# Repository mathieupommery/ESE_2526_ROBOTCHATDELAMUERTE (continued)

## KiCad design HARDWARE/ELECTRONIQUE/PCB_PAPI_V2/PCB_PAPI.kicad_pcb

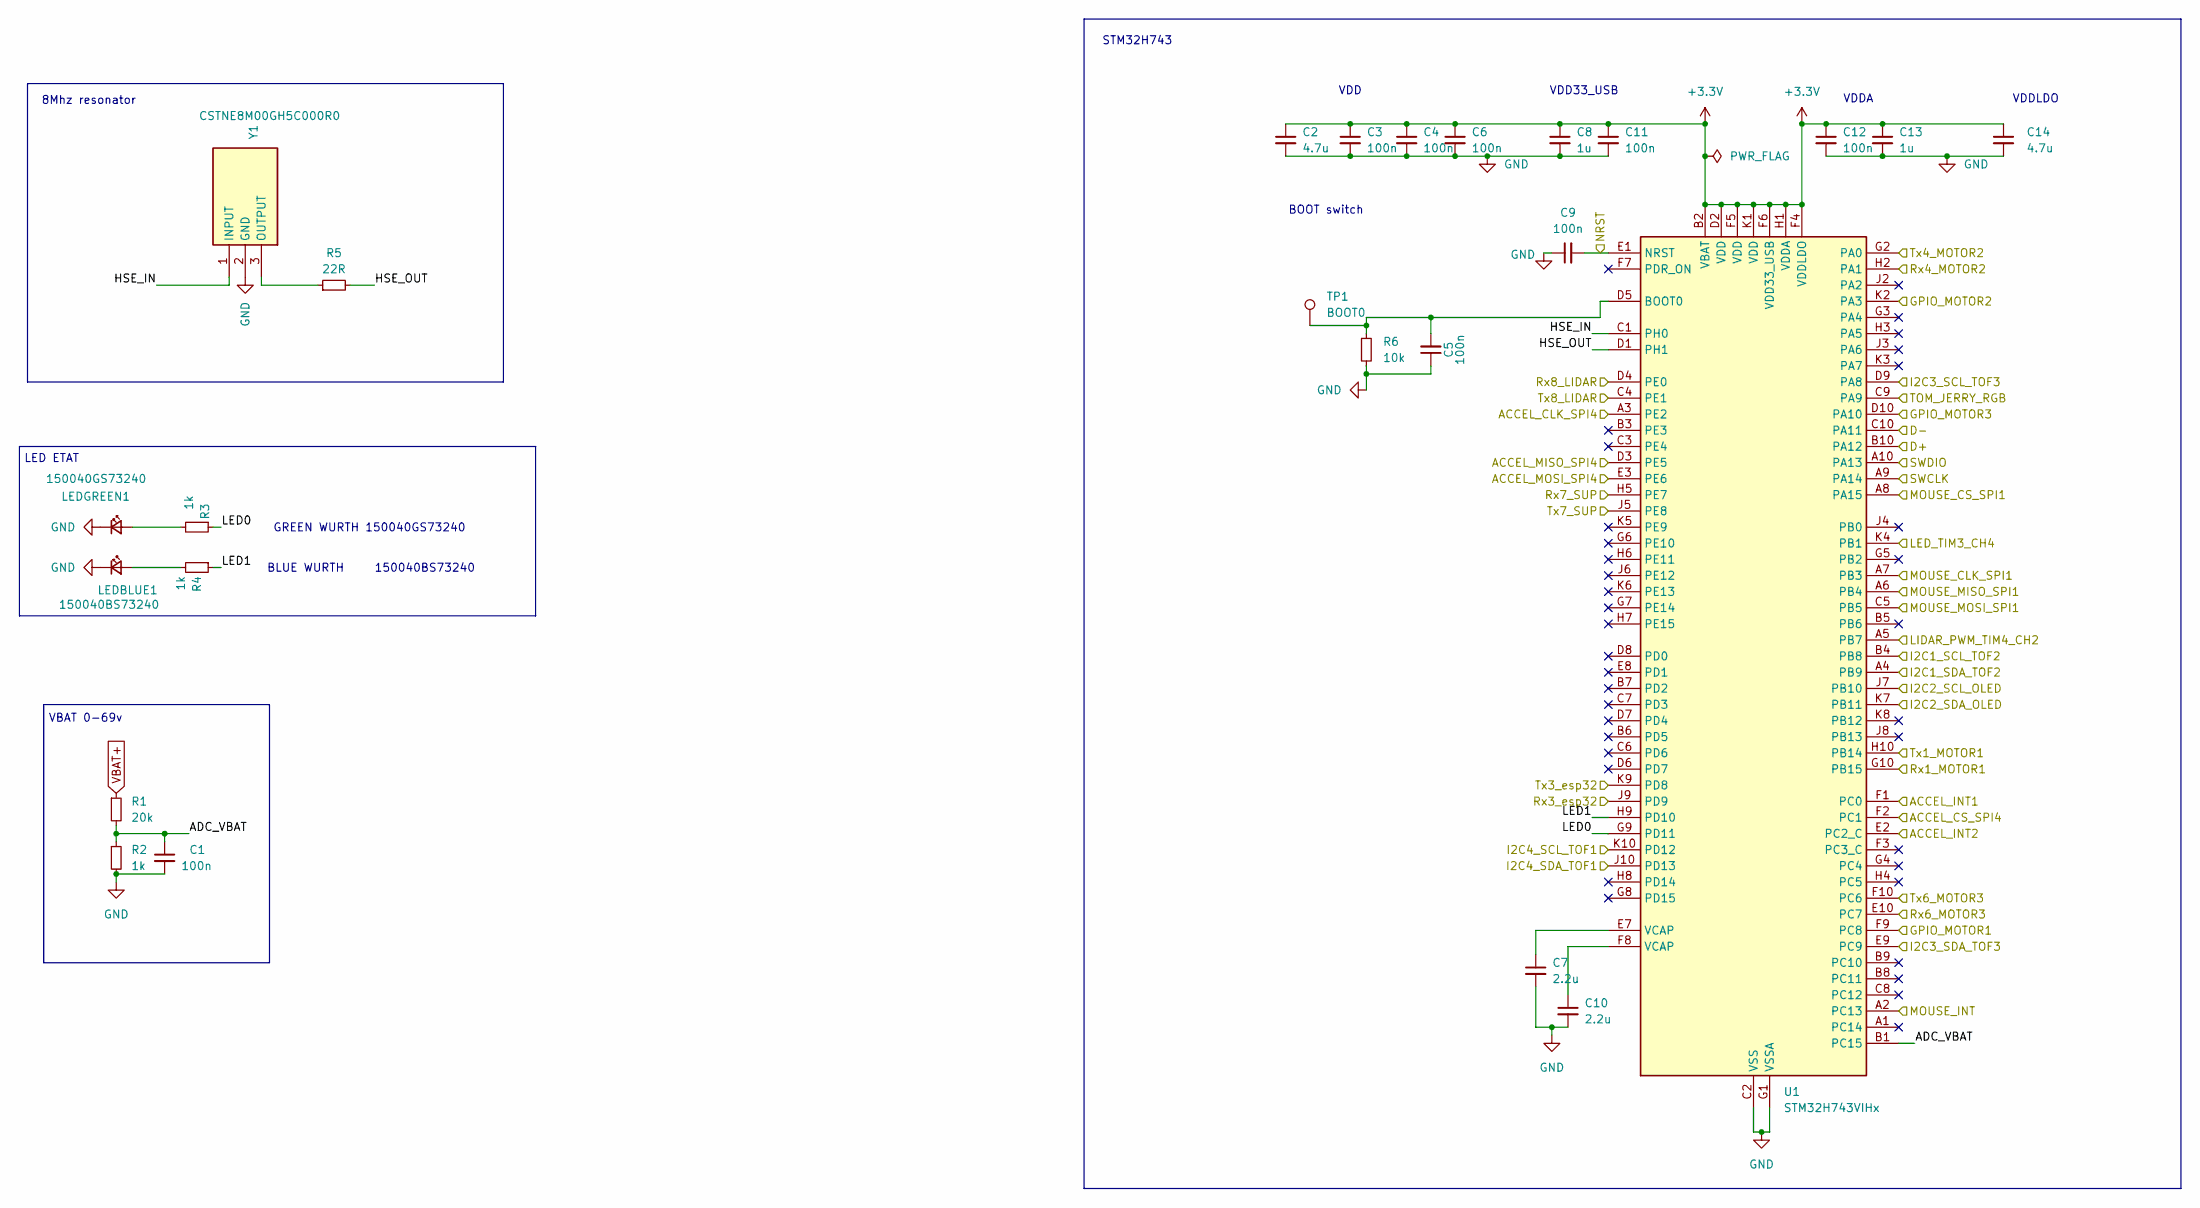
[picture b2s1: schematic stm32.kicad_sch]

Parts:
C1, C3, C5, C9: 100n; C_0201_custom; Manufacturer_Part_Number 885012104005; Mouser Part Number 710-885012104005
C2, C14: 4.7u; C_0402_1005Metric; Manufacturer_Part_Number 885012105008; Mouser Part Number 710-885012105008
C4, C6, C11, C12: 100n; C_0201_0603Metric; Manufacturer_Part_Number 885012104005; Mouser Part Number 710-885012104005
C7, C10: 2.2u; C_0402_1005Metric; Manufacturer_Part_Number 885012105007; Mouser Part Number 710-885012105007
C8, C13: 1u; C_0402_1005Metric; Manufacturer_Part_Number 885012105012; Mouser Part Number 710-885012105012
LEDBLUE1: 150040BS73240; LED_0402_1005Metric; Manufacturer_Part_Number 150040BS73240; Mouser Part Number 710-150040BS73240
LEDGREEN1: 150040GS73240; LED_0402_1005Metric; Manufacturer_Part_Number 150040GS73240; Mouser Part Number 710-150040GS73240
R1: 20k; R_0201_0603Metric; Manufacturer_Part_Number ERJ-1GNF2002C; Mouser Part Number 667-ERJ-1GNF2002C
R2: 1k; R_0201_custom; Manufacturer_Part_Number ERJ-1GNF1001C; Mouser Part Number 667-ERJ-1GNF1001C
R3, R4: 1k; R_0201_0603Metric; Manufacturer_Part_Number ERJ-1GNF1001C; Mouser Part Number 667-ERJ-1GNF1001C
R5: 22R; R_0201_0603Metric; Manufacturer_Part_Number ERJ-1GNF22R0C; Mouser Part Number 667-ERJ-1GNF22R0C
R6: 10k; R_0201_custom; Manufacturer_Part_Number ERJ-1GNF1002C; Mouser Part Number 667-ERJ-1GNF1002C
TP1: BOOT0; pad_0.7mm
U1: STM32H743VIHx; TFBGA-100_8x8mm_Layout10x10_P0.8mm; Manufacturer_Part_Number STM32H743VIH6; Mouser Part Number 511-STM32H743VIH6
Y1: CSTNE8M00GH5C000R0; CSTNE12M0GH5L000R0; Mouser Part Number 81-CSTNE8M00GH5C000R

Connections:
+3.3V: C2.1, C3.1, C4.1, C6.1, C8.1, C11.1, C12.1, C13.1, C14.1, U1.B2 (VBAT), U1.D2 (VDD), U1.F4 (VDDLDO), U1.F5 (VDD), U1.F6 (VDD33_USB), U1.H1 (VDDA), U1.K1 (VDD); also elsewhere on the board
/ACCEL_CLK: U1.A3 (PE2); also elsewhere on the board
/ACCEL_CS: U1.F2 (PC1); also elsewhere on the board
/ACCEL_INT1: U1.F1 (PC0); also elsewhere on the board
/ACCEL_INT2: U1.E2 (PC2_C); also elsewhere on the board
/ACCEL_MISO: U1.D3 (PE5); also elsewhere on the board
/ACCEL_MOSI: U1.E3 (PE6); also elsewhere on the board
/D+STM32: U1.B10 (PA12); also elsewhere on the board
/D-STM32: U1.C10 (PA11); also elsewhere on the board
/ESP32_RX: U1.K9 (PD8); also elsewhere on the board
/ESP32_TX: U1.J9 (PD9); also elsewhere on the board
/GPIO_MOT1: U1.F9 (PC8); also elsewhere on the board
/GPIO_MOT2: U1.K2 (PA3); also elsewhere on the board
/GPIO_MOT3: U1.D10 (PA10); also elsewhere on the board
/LED_TIM: U1.K4 (PB1); also elsewhere on the board
/LIDAR_PWM: U1.A5 (PB7); also elsewhere on the board
/MOUSE_CLK: U1.A7 (PB3); also elsewhere on the board
/MOUSE_CS: U1.A8 (PA15); also elsewhere on the board
/MOUSE_INT: U1.A2 (PC13); also elsewhere on the board
/MOUSE_MISO: U1.A6 (PB4); also elsewhere on the board
/MOUSE_MOSI: U1.C5 (PB5); also elsewhere on the board
/NRST: C9.2, U1.E1 (NRST); also elsewhere on the board
/RGB_TOM_JERRY: U1.C9 (PA9); also elsewhere on the board
/RX_LIDAR: U1.D4 (PE0); also elsewhere on the board
/RX_MOT1: U1.G10 (PB15); also elsewhere on the board
/RX_MOT2: U1.H2 (PA1); also elsewhere on the board
/RX_MOT3: U1.E10 (PC7); also elsewhere on the board
/RX_SUP: U1.H5 (PE7); also elsewhere on the board
/SCL_OLED: U1.J7 (PB10); also elsewhere on the board
/SCL_TOF1: U1.K10 (PD12); also elsewhere on the board
/SCL_TOF2: U1.B4 (PB8); also elsewhere on the board
/SCL_TOF3: U1.D9 (PA8); also elsewhere on the board
/SDA_OLED: U1.K7 (PB11); also elsewhere on the board
/SDA_TOF1: U1.J10 (PD13); also elsewhere on the board
/SDA_TOF2: U1.A4 (PB9); also elsewhere on the board
/SDA_TOF3: U1.E9 (PC9); also elsewhere on the board
/STM32/ADC_VBAT: C1.1, R1.2, R2.1, U1.B1 (PC15)
/STM32/HSE_IN: U1.C1 (PH0), Y1.1 (INPUT)
/STM32/HSE_OUT: R5.2, U1.D1 (PH1)
/STM32/LED0: R3.1, U1.G9 (PD11)
/STM32/LED1: R4.1, U1.H9 (PD10)
/STM32/Tx8_LIDAR: U1.C4 (PE1)
/SWCLK: U1.A9 (PA14); also elsewhere on the board
/SWDIO: U1.A10 (PA13); also elsewhere on the board
/TX_MOT1: U1.H10 (PB14); also elsewhere on the board
/TX_MOT2: U1.G2 (PA0); also elsewhere on the board
/TX_MOT3: U1.F10 (PC6); also elsewhere on the board
/TX_SUP: U1.J5 (PE8); also elsewhere on the board
GND: C1.2, C2.2, C3.2, C4.2, C5.1, C6.2, C7.2, C8.2, C9.1, C10.2, C11.2, C12.2, C13.2, C14.2, LEDBLUE1.1 (K), LEDGREEN1.1 (K), R2.2, R6.2, U1.C2 (VSS), U1.E4 (VSS), U1.E5 (VSS), U1.E6 (VSS), U1.G1 (VSSA), U1.J1 (VSS), Y1.2 (GND); also elsewhere on the board
unnamed: C7.1, U1.E7 (VCAP)
unnamed: C10.1, U1.F8 (VCAP)
unnamed: LEDBLUE1.2 (A), R4.2
unnamed: LEDGREEN1.2 (A), R3.2
unnamed: C5.2, R6.1, TP1.1, U1.D5 (BOOT0)
unnamed: R5.1, Y1.3 (OUTPUT)
VBAT+: R1.1; also elsewhere on the board

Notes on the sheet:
8Mhz resonator
STM32H743
VDD
GREEN WURTH 150040GS73240
VDDA
BOOT switch
LED ETAT
VDD33_USB
VBAT 0-69v
BLUE WURTH 150040BS73240
VDDLDO

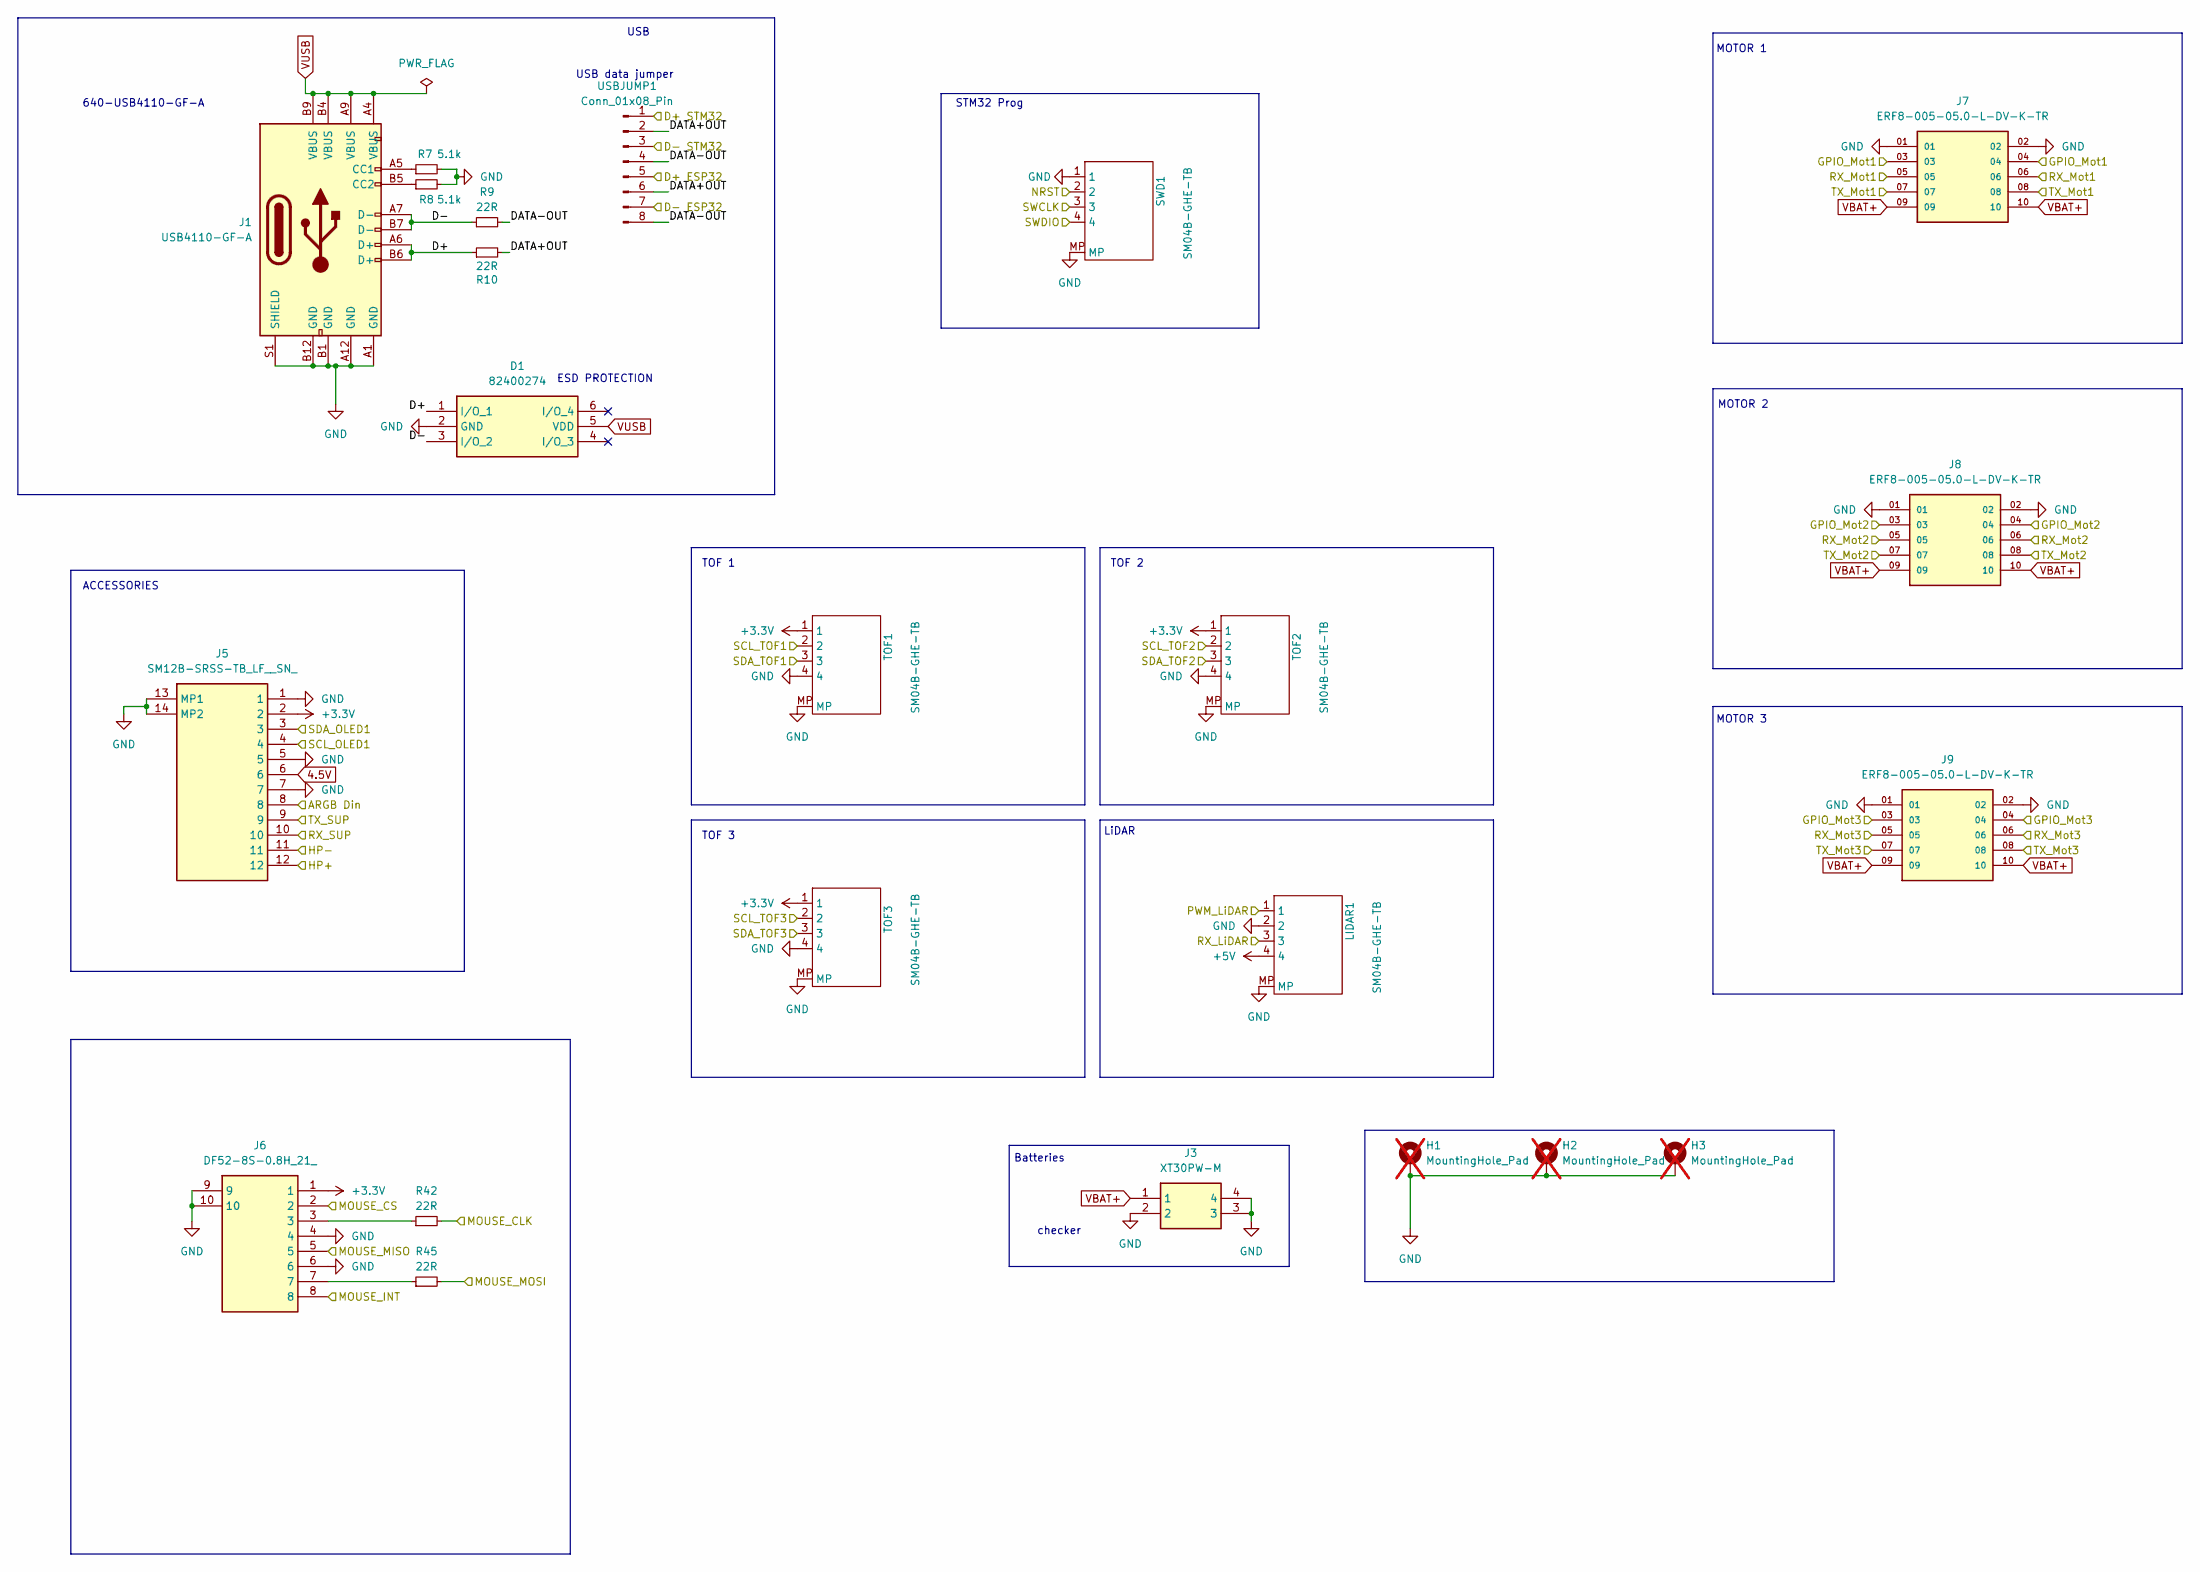
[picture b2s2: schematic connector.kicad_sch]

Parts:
D1: 82400274; SOT65P210X110-6N; Mouser Part Number 710-82400274
H1, H2, H3: MountingHole_Pad; MountingHole_2.5mm_Pad_Via; not fitted
J1: USB4110-GF-A; USB_C_Receptacle_GCT_USB4110; Manufacturer_Part_Number USB4110-GF-A; Mouser Part Number 640-USB4110-GF-A
J3: XT30PW-M; XT30PWM; Manufacturer_Part_Number XT30PW-M
J5: SM12B-SRSS-TB_LF__SN_; SM12BSRSSTBLFSN; Manufacturer_Part_Number SM12B-SRSS-TB(LF)(SN); Mouser Part Number N/A
J6: DF52-8S-0.8H_21_; DF528S08H21; Manufacturer_Part_Number DF52-8S-0.8H(21); Mouser Part Number 798-DF52-8S-0.8H21
J7, J8, J9: ERF8-005-05.0-L-DV-K-TR; SAMTEC_ERF8-005-05.0-L-DV-K-TR
LIDAR1: SM04B-GHE-TB; JST_GH_BM04B-GHS-TBT_1x04-1MP_P1.25mm_Vertical; Manufacturer_Part_Number SM04B-GHE-TB; Mouser Part Number 306-SM04BGHETBLFSN
R7, R8: 5.1k; R_0201_custom; Manufacturer_Part_Number ERJ-1GNF5101C; Mouser Part Number 667-ERJ-1GNF5101C
R9, R10, R42, R45: 22R; R_0201_0603Metric; Manufacturer_Part_Number ERJ-1GNF22R0C; Mouser Part Number 667-ERJ-1GNF22R0C
SWD1: SM04B-GHE-TB; JST_GH_BM04B; Manufacturer_Part_Number SM04B-GHE-TB; Mouser Part Number 306-SM04BGHETBLFSN
TOF1, TOF2, TOF3: SM04B-GHE-TB; JST_GH_BM04B; Manufacturer_Part_Number SM04B-GHE-TB; Mouser Part Number 306-SM04BGHETBLFSN
USBJUMP1: Conn_01x08_Pin; PinHeader_2x04_P1.27mm_Vertical_SMD

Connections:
4.5V: J5.6; also elsewhere on the board
+3.3V: J5.2, J6.1, TOF1.1, TOF2.1, TOF3.1; also elsewhere on the board
+5V: LIDAR1.4; also elsewhere on the board
/CONNECTOR/D+: D1.1 (I/O_1), J1.A6 (D+), J1.B6 (D+), R10.1
/CONNECTOR/D-: D1.3 (I/O_2), J1.A7 (D-), J1.B7 (D-), R9.1
/CONNECTOR/DATA+OUT: R10.2, USBJUMP1.2, USBJUMP1.6
/CONNECTOR/DATA-OUT: R9.2, USBJUMP1.4, USBJUMP1.8
/D+ESP32: USBJUMP1.5; also elsewhere on the board
/D+STM32: USBJUMP1.1; also elsewhere on the board
/D-ESP32: USBJUMP1.7; also elsewhere on the board
/D-STM32: USBJUMP1.3; also elsewhere on the board
/GPIO_MOT1: J7.03, J7.04; also elsewhere on the board
/GPIO_MOT2: J8.03, J8.04; also elsewhere on the board
/GPIO_MOT3: J9.03, J9.04; also elsewhere on the board
/HP+: J5.12; also elsewhere on the board
/HP-: J5.11; also elsewhere on the board
/LED_TIM: J5.8; also elsewhere on the board
/LIDAR_PWM: LIDAR1.1; also elsewhere on the board
/MOUSE_CLK: R42.2; also elsewhere on the board
/MOUSE_CS: J6.2; also elsewhere on the board
/MOUSE_INT: J6.8; also elsewhere on the board
/MOUSE_MISO: J6.5; also elsewhere on the board
/MOUSE_MOSI: R45.2; also elsewhere on the board
/NRST: SWD1.2; also elsewhere on the board
/RX_LIDAR: LIDAR1.3; also elsewhere on the board
/RX_MOT1: J7.05, J7.06; also elsewhere on the board
/RX_MOT2: J8.05, J8.06; also elsewhere on the board
/RX_MOT3: J9.05, J9.06; also elsewhere on the board
/RX_SUP: J5.10; also elsewhere on the board
/SCL_OLED: J5.4; also elsewhere on the board
/SCL_TOF1: TOF1.2; also elsewhere on the board
/SCL_TOF2: TOF2.2; also elsewhere on the board
/SCL_TOF3: TOF3.2; also elsewhere on the board
/SDA_OLED: J5.3; also elsewhere on the board
/SDA_TOF1: TOF1.3; also elsewhere on the board
/SDA_TOF2: TOF2.3; also elsewhere on the board
/SDA_TOF3: TOF3.3; also elsewhere on the board
/SWCLK: SWD1.3; also elsewhere on the board
/SWDIO: SWD1.4; also elsewhere on the board
/TX_MOT1: J7.07, J7.08; also elsewhere on the board
/TX_MOT2: J8.07, J8.08; also elsewhere on the board
/TX_MOT3: J9.07, J9.08; also elsewhere on the board
/TX_SUP: J5.9; also elsewhere on the board
GND: D1.2 (GND), H1.1, H2.1, H3.1, J1.A1 (GND), J1.A12 (GND), J1.B1 (GND), J1.B12 (GND), J1.S1 (SHIELD), J3.2, J3.3, J3.4, J5.1, J5.5, J5.7, J5.13 (MP1), J5.14 (MP2), J6.4, J6.6, J6.9, J6.10, J7.01, J7.02, J8.01, J8.02, J9.01, J9.02, LIDAR1.2, LIDAR1.MP, R7.2, R8.2, SWD1.1, SWD1.MP, TOF1.4, TOF1.MP, TOF2.4, TOF2.MP, TOF3.4, TOF3.MP; also elsewhere on the board
unnamed: J1.A5 (CC1), R7.1
unnamed: J1.B5 (CC2), R8.1
unnamed: J6.3, R42.1
unnamed: J6.7, R45.1
VBAT+: J3.1, J7.09, J7.10, J8.09, J8.10, J9.09, J9.10; also elsewhere on the board
VUSB: D1.5 (VDD), J1.A4 (VBUS), J1.A9 (VBUS), J1.B4 (VBUS), J1.B9 (VBUS); also elsewhere on the board

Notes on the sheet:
Batteries
TOF 2
LiDAR
ACCESSORIES
checker
USB data jumper
MOTOR 2
MOTOR 3
TOF 1
640-USB4110-GF-A
TOF 3
STM32 Prog
USB
MOTOR 1
ESD PROTECTION

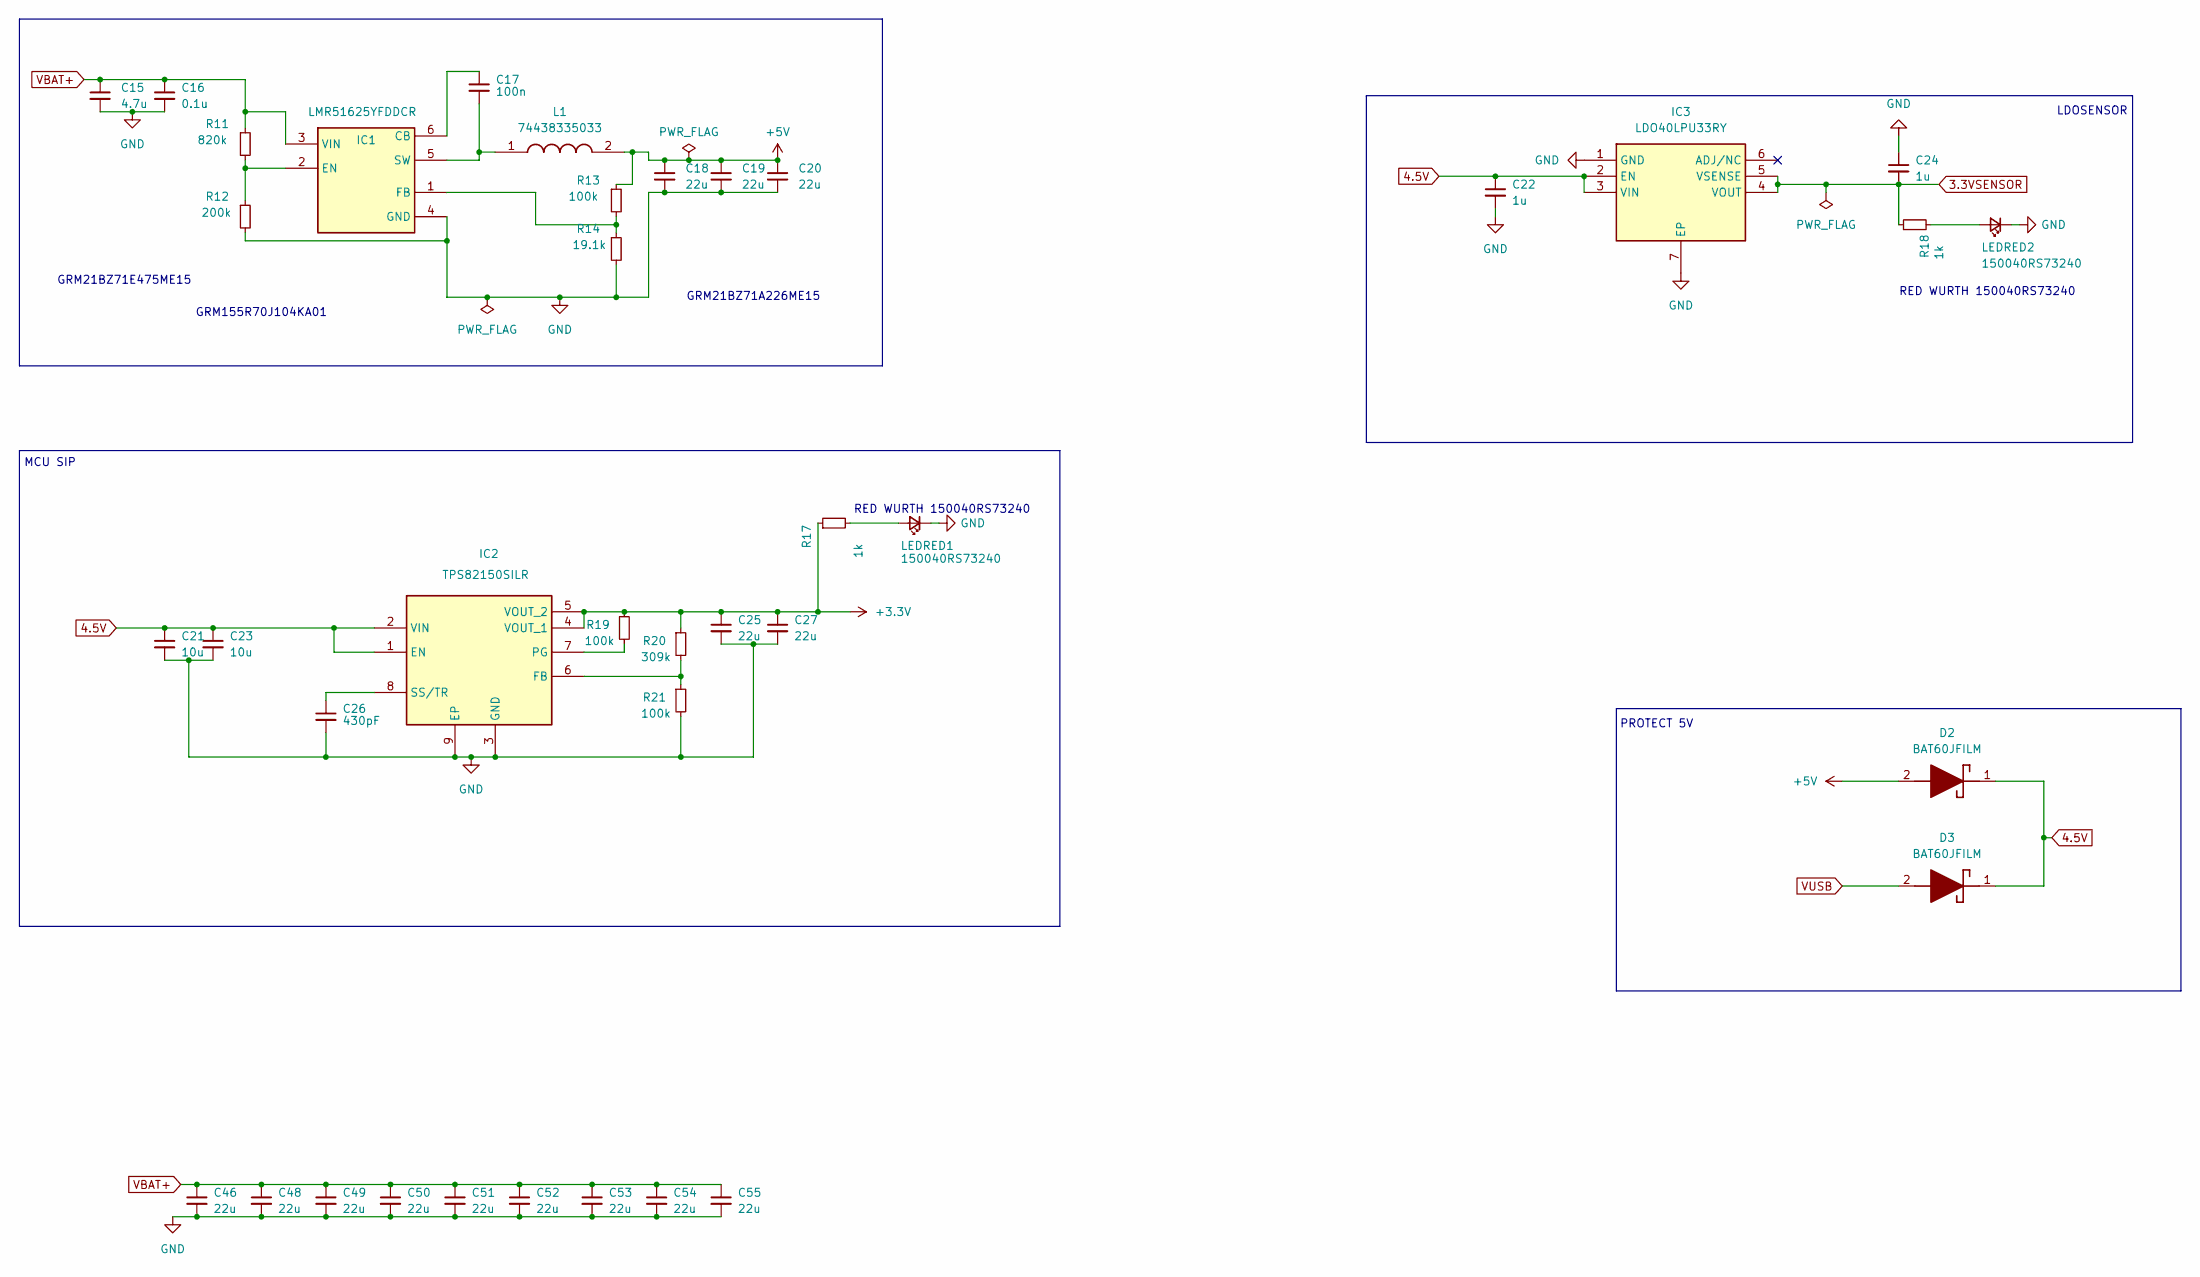
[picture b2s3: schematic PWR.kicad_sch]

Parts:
C15: 4.7u; C_0805_2012Metric
C16: 0.1u; C_0402_1005Metric
C17: 100n; C_0201_0603Metric
C18, C19, C20, C46, C48, C49, C50, C51, C52, C53, C54, C55: 22u; C_0805_2012Metric
C21, C23: 10u; C_0603_1608Metric; Manufacturer_Part_Number 885012105012; Mouser Part Number 710-885012105012
C22, C24: 1u; C_0402_1005Metric; Manufacturer_Part_Number 885012105012; Mouser Part Number 710-885012105012
C25, C27: 22u; C_0603_1608Metric; Manufacturer_Part_Number 885012105012; Mouser Part Number 710-885012105012
C26: 430pF; C_0201_0603Metric
D2, D3: BAT60JFILM; SOD2513X117N; Mouser Part Number 511-BAT60JFILM
IC1: LMR51625YFDDCR; SOT95P280X110-6N; Manufacturer_Part_Number LMR51625YFDDCR; Mouser Part Number 595-LMR51625YFDDCR
IC2: TPS82150SILR; TPS82130SILT; Manufacturer_Part_Number TPS82150SILR; Mouser Part Number 595-TPS82150SILR
IC3: LDO40LPU33RY; SON95P300X300X90-7N-D; Manufacturer_Part_Number LDO40LPU33RY; Mouser Part Number 511-LDO40LPU33RY
L1: 74438335033; INDC3030X150N; Manufacturer_Part_Number 74438335033; Mouser Part Number 710-74438335033
LEDRED1, LEDRED2: 150040RS73240; LED_0402_1005Metric; Manufacturer_Part_Number 150040RS73240; Mouser Part Number 710-150040RS73240
R11: 820k; R_0201_0603Metric
R12: 200k; R_0201_custom
R13, R19, R21: 100k; R_0201_0603Metric
R14: 19.1k; R_0201_custom
R17: 1k; R_0201_0603Metric; Manufacturer_Part_Number ERJ-1GNF1001C; Mouser Part Number 667-ERJ-1GNF1001C
R18: 1k; R_0201_custom; Manufacturer_Part_Number ERJ-1GNF1001C; Mouser Part Number 667-ERJ-1GNF1001C
R20: 309k; R_0201_0603Metric

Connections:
3.3VSENSOR: C24.2, IC3.4 (VOUT), IC3.5 (VSENSE), R18.1; also elsewhere on the board
4.5V: C21.1, C22.1, C23.1, D2.1 (K), D3.1 (K), IC2.1 (EN), IC2.2 (VIN), IC3.2 (EN), IC3.3 (VIN); also elsewhere on the board
+3.3V: C25.1, C27.1, IC2.4 (VOUT_1), IC2.5 (VOUT_2), R17.1, R19.1, R20.1; also elsewhere on the board
+5V: C18.1, C19.1, C20.1, D2.2 (A), L1.2, R13.1; also elsewhere on the board
GND: C15.2, C16.2, C18.2, C19.2, C20.2, C21.2, C22.2, C23.2, C24.1, C25.2, C26.2, C27.2, C46.2, C48.2, C49.2, C50.2, C51.2, C52.2, C53.2, C54.2, C55.2, IC1.4 (GND), IC2.3 (GND), IC2.9 (EP), IC3.1 (GND), IC3.7 (EP), LEDRED1.1 (K), LEDRED2.1 (K), R12.2, R14.2, R21.2; also elsewhere on the board
unnamed: C17.1, IC1.6 (CB)
unnamed: IC1.2 (EN), R11.2, R12.1
unnamed: IC1.1 (FB), R13.2, R14.1
unnamed: C17.2, IC1.5 (SW), L1.1
unnamed: IC2.6 (FB), R20.2, R21.1
unnamed: IC2.7 (PG), R19.2
unnamed: C26.1, IC2.8 (SS/TR)
unnamed: LEDRED1.2 (A), R17.2
unnamed: LEDRED2.2 (A), R18.2
VBAT+: C15.1, C16.1, C46.1, C48.1, C49.1, C50.1, C51.1, C52.1, C53.1, C54.1, C55.1, IC1.3 (VIN), R11.1; also elsewhere on the board
VUSB: D3.2 (A); also elsewhere on the board

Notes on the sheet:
GRM21BZ71E475ME15
GRM21BZ71A226ME15
RED WURTH 150040RS73240
LDOSENSOR
MCU SIP
PROTECT 5V
GRM155R70J104KA01

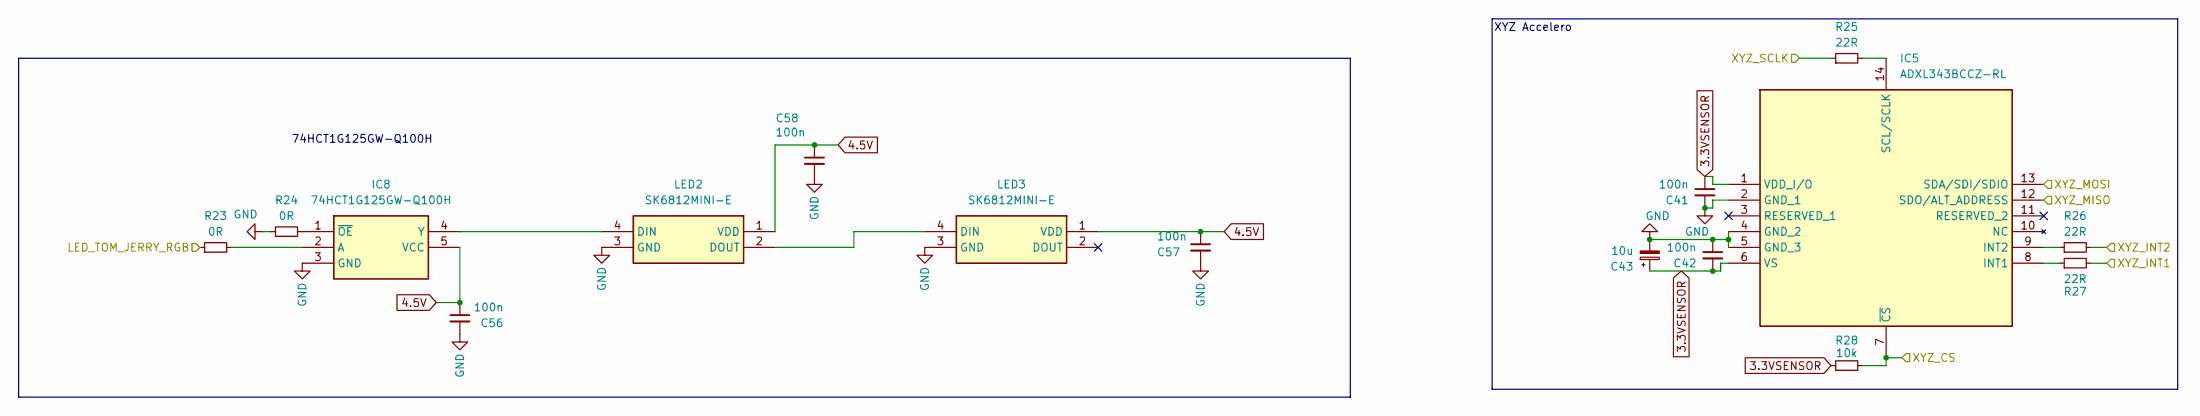
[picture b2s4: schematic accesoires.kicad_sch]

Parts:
C41: 100n; C_0201_0603Metric
C42, C56, C57, C58: 100n; C_0201_custom
C43: 10u; CP_EIA-1608-08_AVX-J
IC5: ADXL343BCCZ-RL; ADXL343BCCZRL; Manufacturer_Part_Number ADXL343BCCZ-RL; Mouser Part Number 584-ADXL343BCCZ-R
IC8: 74HCT1G125GW-Q100H; Manufacturer_Part_Number 74HCT1G125GW-Q100H; Mouser Part Number 77174HCT1G125GWQ100H
LED2, LED3: SK6812MINI-E; SK6812MINIE; Manufacturer_Part_Number SK6812MINI-E
R23, R24: 0R; R_0201_custom; Manufacturer_Part_Number ERJ-1GNF1000C; Mouser Part Number 667-ERJ-1GNF1000C
R25: 22R; R_0201_custom; Manufacturer_Part_Number ERJ-1GNF1000C; Mouser Part Number 667-ERJ-1GNF1000C
R26, R27: 22R; R_0201_0603Metric; Manufacturer_Part_Number ERJ-1GNF1000C; Mouser Part Number 667-ERJ-1GNF1000C
R28: 10k; R_0201_0603Metric; Manufacturer_Part_Number ERJ-1GNF1000C; Mouser Part Number 667-ERJ-1GNF1000C

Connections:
3.3VSENSOR: C41.1, C42.2, C43.1, IC5.1 (VDD_I/O), IC5.6 (VS), R28.1; also elsewhere on the board
4.5V: C56.1, C57.1, C58.1, IC8.5 (VCC), LED2.1 (VDD), LED3.1 (VDD); also elsewhere on the board
/ACCEL_CLK: R25.1; also elsewhere on the board
/ACCEL_CS: IC5.7 (~CS), R28.2; also elsewhere on the board
/ACCEL_INT1: R27.2; also elsewhere on the board
/ACCEL_INT2: R26.2; also elsewhere on the board
/ACCEL_MISO: IC5.12 (SDO/ALT_ADDRESS); also elsewhere on the board
/ACCEL_MOSI: IC5.13 (SDA/SDI/SDIO); also elsewhere on the board
/RGB_TOM_JERRY: R23.1; also elsewhere on the board
GND: C41.2, C42.1, C43.2, C56.2, C57.2, C58.2, IC5.2 (GND_1), IC5.4 (GND_2), IC5.5 (GND_3), IC8.3 (GND), LED2.3 (GND), LED3.3 (GND), R24.1; also elsewhere on the board
unnamed: IC5.8 (INT1), R27.1
unnamed: IC5.9 (INT2), R26.1
unnamed: IC5.14 (SCL/SCLK), R25.2
unnamed: IC8.2 (A), R23.2
unnamed: IC8.4 (Y), LED2.4 (DIN)
unnamed: IC8.1 (~OE), R24.2
unnamed: LED2.2 (DOUT), LED3.4 (DIN)

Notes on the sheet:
XYZ Accelero
74HCT1G125GW-Q100H
